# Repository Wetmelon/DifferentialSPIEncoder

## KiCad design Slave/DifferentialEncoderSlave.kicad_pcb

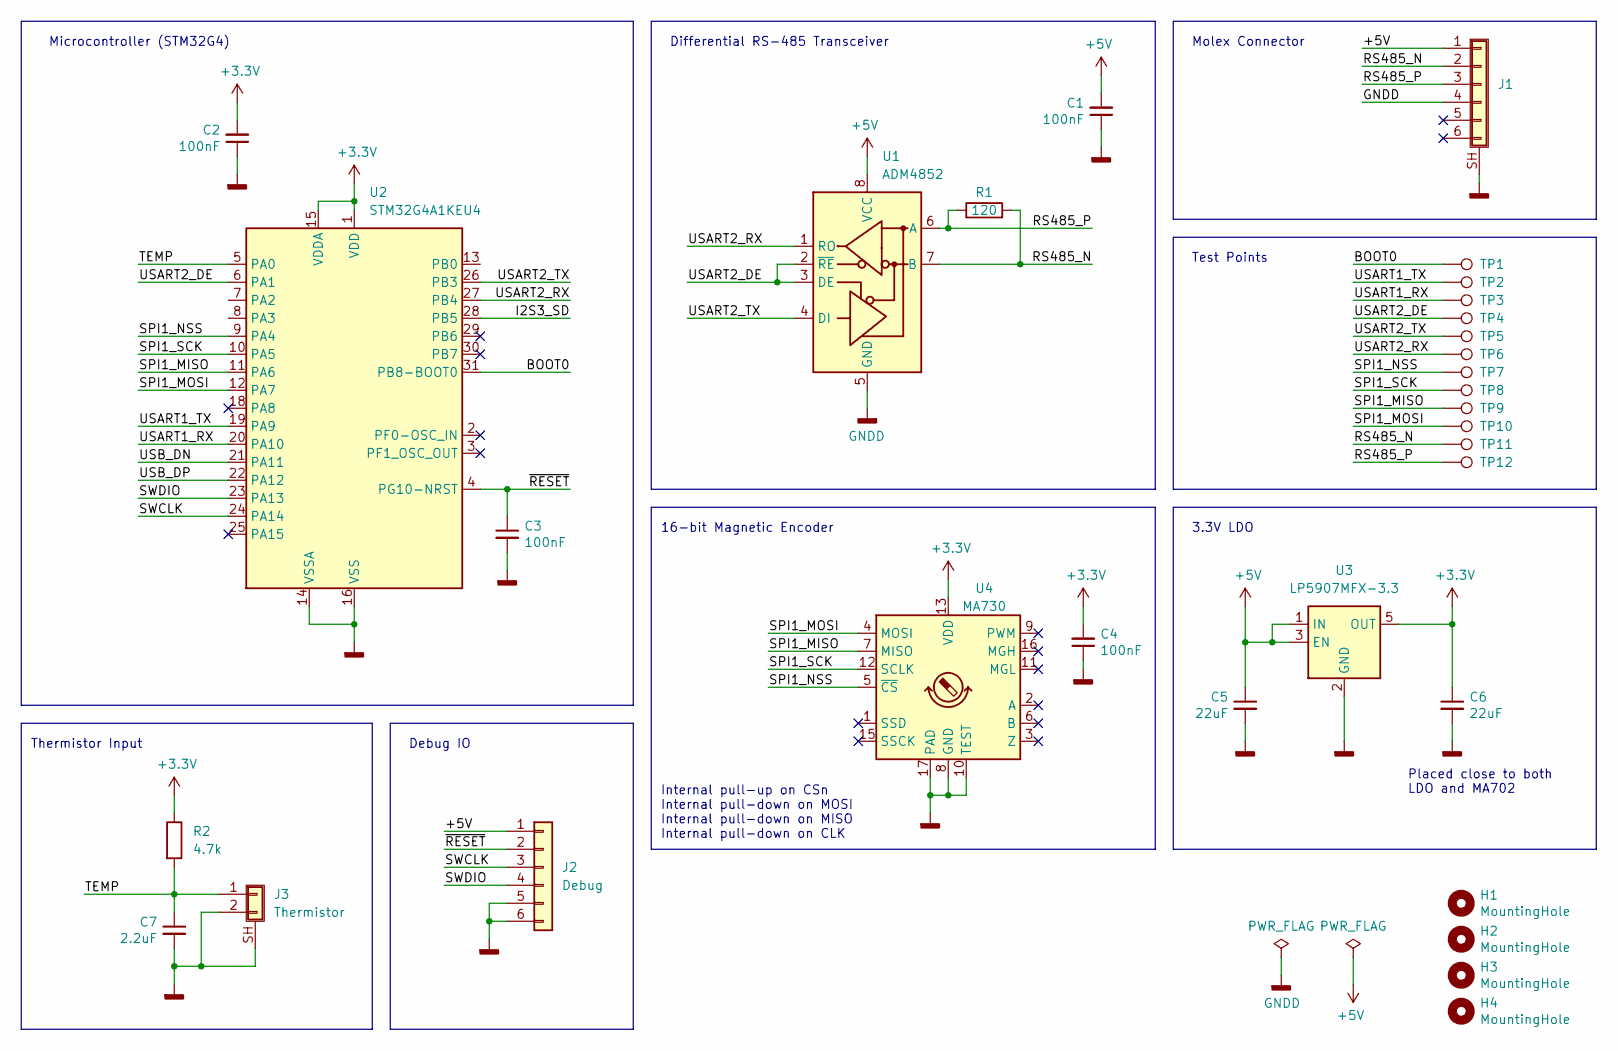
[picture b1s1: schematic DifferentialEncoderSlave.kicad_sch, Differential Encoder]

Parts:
C1, C2, C3, C4: 100nF; C_0402_1005Metric
C5, C6: 22uF; C_0805_2012Metric
C7: 2.2uF; C_0402_1005Metric
H1, H2, H3, H4: MountingHole; MountingHole_3mm
J1: (no value)
J2: Debug; Tag-Connect_TC2030-IDC-NL_2x03_P1.27mm_Vertical
J3: Thermistor; JST_GH_SM02B
R1: 120; R_0402_1005Metric
R2: 4.7k; R_0402_1005Metric
TP1, TP2, TP3, TP4, TP5, TP6, TP7, TP8, TP9, TP10, TP11, TP12: TestPoint; TestPoint_Pad_D1.0mm
U1: ADM4852; LFCSP-8-1EP_3x3mm_P0.5mm_EP1.45x1.74mm
U2: STM32G4A1KEU4; UFQFPN-32-1EP_5x5mm_P0.5mm_EP3.5x3.5mm
U3: LP5907MFX-3.3; SOT-23-5
U4: MA730; QFN-16-1EP_3x3mm_P0.5mm_EP1.7x1.7mm

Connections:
+3V3: C2.2, C4.2, C6.1, R2.1, U2.1 (VDD), U2.15 (VDDA), U2.17 (VDD), U3.5 (OUT), U4.13 (VDD)
+5V: C1.2, C5.1, J1.1, J2.1, U1.8 (VCC), U3.1 (IN), U3.3 (EN)
/BOOT0: TP1.1, U2.31 (PB8-BOOT0)
/I2S3_SD: U2.28 (PB5)
/RS485_N: J1.2, R1.2, TP11.1, U1.7 (B)
/RS485_P: J1.3, R1.1, TP12.1, U1.6 (A)
/SPI1_MISO: TP9.1, U2.11 (PA6), U4.7 (MISO)
/SPI1_MOSI: TP10.1, U2.12 (PA7), U4.4 (MOSI)
/SPI1_NSS: TP7.1, U2.9 (PA4), U4.5 (~CS)
/SPI1_SCK: TP8.1, U2.10 (PA5), U4.12 (SCLK)
/SWCLK: J2.3, U2.24 (PA14)
/SWDIO: J2.4, U2.23 (PA13)
/TEMP: C7.1, J3.1, R2.2, U2.5 (PA0)
/USART1_RX: TP3.1, U2.20 (PA10)
/USART1_TX: TP2.1, U2.19 (PA9)
/USART2_DE: TP4.1, U1.2 (~RE), U1.3 (DE), U2.6 (PA1)
/USART2_RX: TP6.1, U1.1 (RO), U2.27 (PB4)
/USART2_TX: TP5.1, U1.4 (DI), U2.26 (PB3)
/USB_DN: U2.21 (PA11)
/USB_DP: U2.22 (PA12)
/~RESET: C3.1, J2.2, U2.4 (PG10-NRST)
GNDD: C1.1, C2.1, C3.2, C4.1, C5.2, C6.2, C7.2, J1.4, J1.SH (Shield), J2.5, J2.6, J3.2, J3.SH (Shield), U1.5 (GND), U1.PAD, U2.14 (VSSA), U2.16 (VSS), U2.32 (VSS), U2.33 (PAD), U3.2 (GND), U4.8 (GND), U4.10 (TEST), U4.17 (PAD)

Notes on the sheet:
Test Points
Thermistor Input
Internal pull-up on CSn Internal pull-down on MOSI Internal pull-down on MISO Internal pull-down on CLK
16-bit Magnetic Encoder
Placed close to both LDO and MA702
3.3V LDO
Differential RS-485 Transceiver
Microcontroller (STM32G4)
Molex Connector
Debug IO

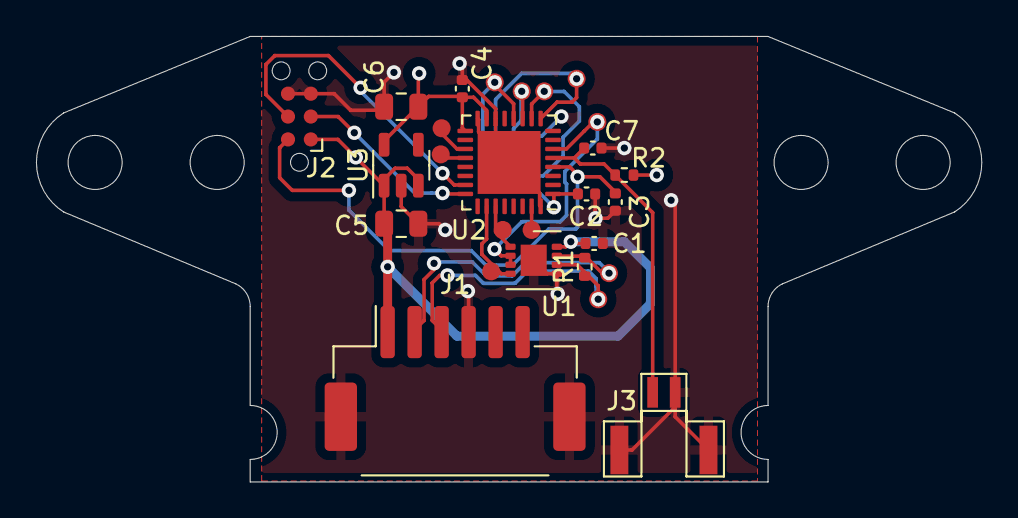
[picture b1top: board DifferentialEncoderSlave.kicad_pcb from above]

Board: 4 copper layers, 52.5 x 24.8 mm, 32 parts (1 on the bottom side), 19 nets.

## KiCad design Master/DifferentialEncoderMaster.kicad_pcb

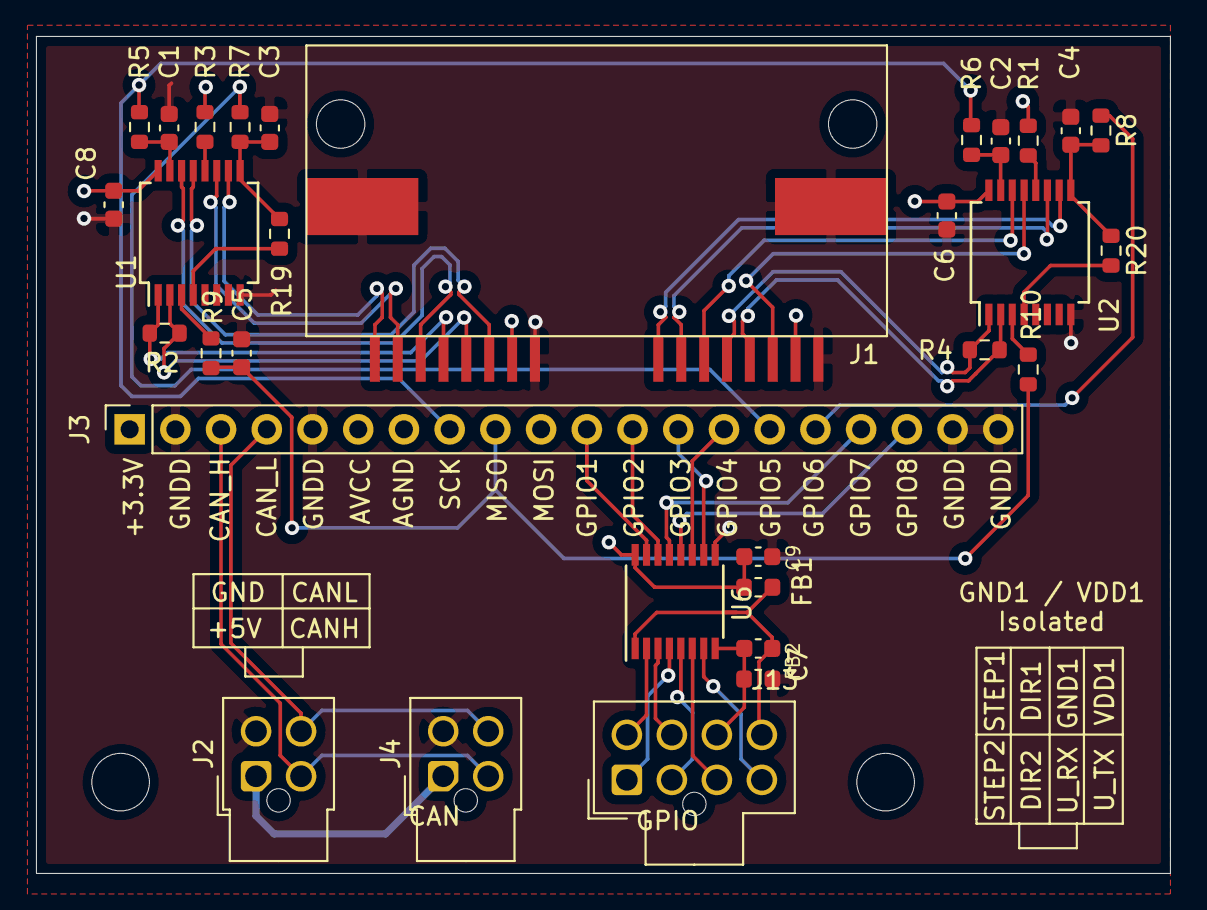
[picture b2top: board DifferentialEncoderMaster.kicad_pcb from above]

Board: 4 copper layers, 63.0 x 46.5 mm, 33 parts (0 on the bottom side), 45 nets.

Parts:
C1, C2, C3, C4, C5: 22pF; C_0603_1608Metric
C6, C7, C8, C9: 100nF; C_0603_1608Metric
FB1, FB2: 1kR; L_0603_1608Metric
H1, H2: MountingHole; MountingHole_3.2mm_M3
J1: RJ45_Shielded_x2; RJ45_RJSSE5380-02
J2, J4: CAN; Molex_Nano-Fit_105310-xx04_2x02_P2.50mm_Vertical
J3: Conn_01x20; PinSocket_1x20_P2.54mm_Vertical
J13: ISO_GPIO; Molex_Nano-Fit_105310-xx08_2x04_P2.50mm_Vertical
R1, R3: 3.3k; R_0603_1608Metric
R2, R4: 100; R_0603_1608Metric
R5, R6, R7, R8, R9, R10: 680; R_0603_1608Metric
R19, R20: 0R; R_0603_1608Metric
U1, U2: SN75C1167; SSOP-16_5.3x6.2mm_P0.65mm
U6: ISO7761DBQ; SSOP-16_3.9x4.9mm_P0.635mm

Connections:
+5V: C6.1, C8.1, C9.1, FB1.2, J1.7, J1.15, R1.1, R3.1, U1.16, U2.16, U6.16
/+12V: J2.1, J4.1
/CAN_H: J2.2, J3.3, J4.2
/CAN_L: J2.4, J3.4, J4.4
/CLK_1: C1.1, R5.2, U1.15
/CLK_1+: J1.3, U1.14
/CLK_1-: J1.6, U1.13
/CLK_2: C2.1, R6.2, U2.15
/CLK_2+: J1.11, U2.14
/CLK_2-: J1.14, U2.13
/CSn_1: C3.1, R7.2, R19.1, U1.9
/CSn_1+: J1.1, U1.10
/CSn_1-: J1.2, U1.11
/CSn_2: C4.1, R8.2, R20.1, U2.9
/CSn_2+: J1.9, U2.10
/CSn_2-: J1.10, U2.11
/GPIO1: J3.11, U6.15
/GPIO2: J3.12, U6.14
/GPIO3: J3.13, U6.10
/GPIO4: J3.14, U6.11
/GPIO5: J3.15, R7.1
/GPIO6: J3.16, R8.1
/GPIO7: J3.17, U6.13
/GPIO8: J3.18, U6.12
/ISO_DIR_1: J13.6, U6.3
/ISO_DIR_2: J13.2, U6.5
/ISO_STEP_1: J13.5, U6.2
/ISO_STEP_2: J13.1, U6.4
/ISO_UART_RX: J13.3, U6.6
/ISO_UART_TX: J13.4, U6.7
/MISO: C5.1, J3.9, R9.2, R10.2
/MISO_1: R9.1, U1.3
/MISO_1+: J1.5, R2.1, U1.2
/MISO_1-: J1.4, R2.2, U1.1
/MISO_2: R10.1, U2.3
/MISO_2+: J1.13, R4.1, U2.2
/MISO_2-: J1.12, R4.2, U2.1
/SCK: J3.8, R5.1, R6.1
GND1: C7.2, FB2.1, J13.7, U6.8
GNDD: C1.2, C2.2, C3.2, C4.2, C5.2, C6.2, C8.2, C9.2, FB2.2, J1.8, J1.16, J1.SH, J2.3, J3.2, J3.5, J3.19, J3.20, J4.3, U1.8, U2.8, U6.9
unnamed: R1.2, U2.12
unnamed: R3.2, U1.12
unnamed: R19.2, U1.4
unnamed: R20.2, U2.4
VDD1: C7.1, FB1.1, J13.8, U6.1

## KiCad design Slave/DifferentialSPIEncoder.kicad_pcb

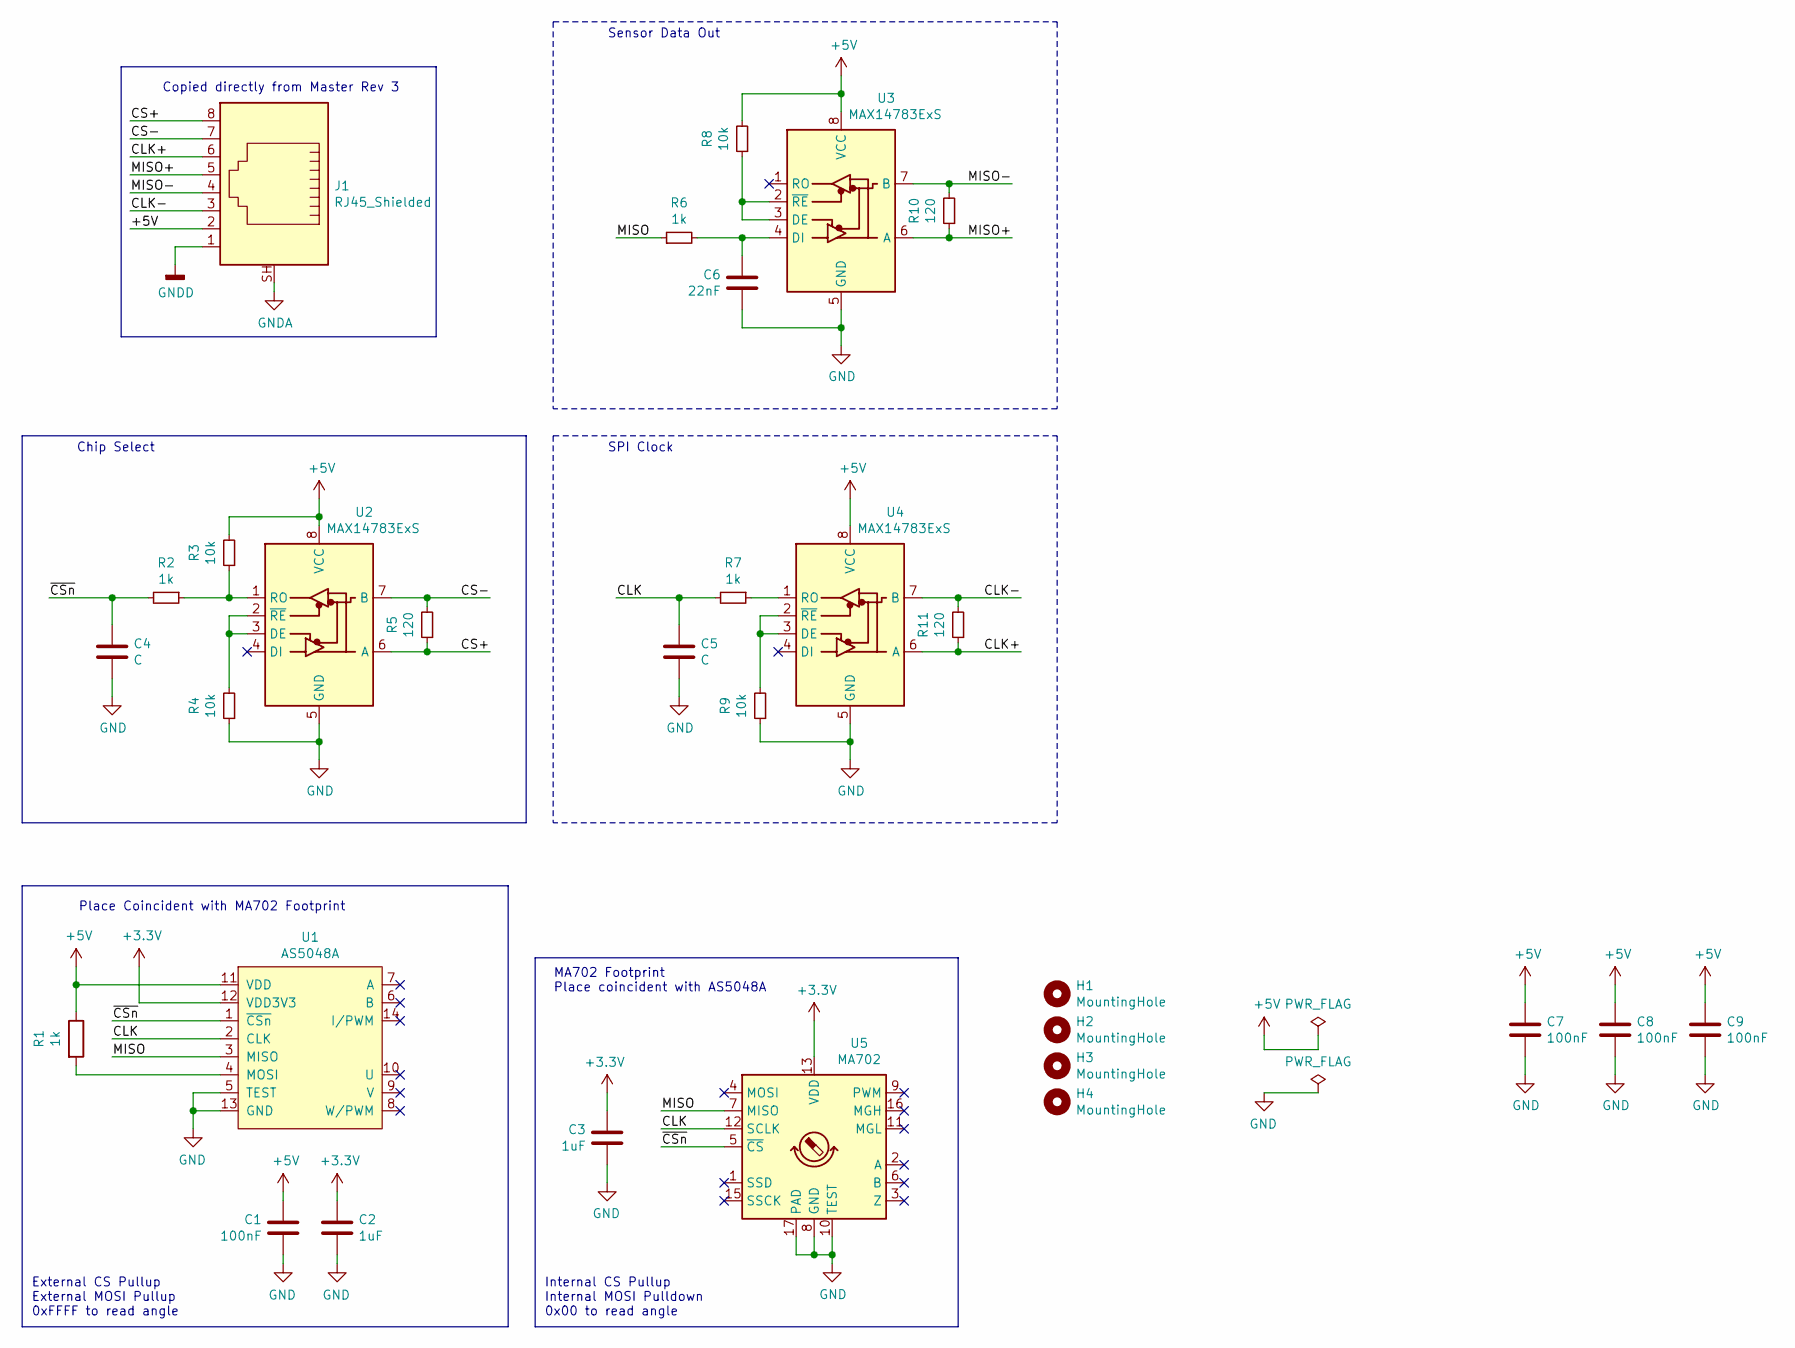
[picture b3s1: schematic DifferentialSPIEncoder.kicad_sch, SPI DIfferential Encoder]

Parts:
C1, C7, C8, C9: 100nF; C_0603_1608Metric
C2, C3: 1uF; C_0603_1608Metric
C4, C5: C; C_0603_1608Metric
C6: 22nF; C_0603_1608Metric
H1, H2: MountingHole; MountingHole_3mm
H3, H4: MountingHole; MountingHole_3.2mm_M3
J1: RJ45_Shielded; RJ45_Amphenol_RJHSE5380
R1, R2, R6, R7: 1k; R_0603_1608Metric
R3, R4, R8, R9: 10k; R_0603_1608Metric
R5, R10, R11: 120; R_0603_1608Metric
U1: AS5048A; TSSOP-14_4.4x5mm_P0.65mm
U2, U3, U4: MAX14783ExS; SOIC-8_3.9x4.9mm_P1.27mm
U5: MA702; QFN-16-1EP_3x3mm_P0.5mm_EP1.8x1.8mm

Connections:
+3V3: C2.1, C3.1, U1.12 (VDD3V3), U5.13 (VDD)
+5V: C1.1, C7.1, C8.1, C9.1, J1.2, R1.1, R3.2, R8.2, U1.11 (VDD), U2.8 (VCC), U3.8 (VCC), U4.8 (VCC)
/CLK: C5.1, R7.2, U1.2 (CLK), U5.12 (SCLK)
/CLK+: J1.6, R11.1, U4.6 (A)
/CLK-: J1.3, R11.2, U4.7 (B)
/CS+: J1.8, R5.1, U2.6 (A)
/CS-: J1.7, R5.2, U2.7 (B)
/MISO: R6.1, U1.3 (MISO), U5.7 (MISO)
/MISO+: J1.5, R10.1, U3.6 (A)
/MISO-: J1.4, R10.2, U3.7 (B)
/~CSn: C4.1, R2.2, U1.1 (~CSn), U5.5 (~CS)
GND: C1.2, C2.2, C3.2, C4.2, C5.2, C6.2, C7.2, C8.2, C9.2, R4.1, R9.1, U1.5 (TEST), U1.13 (GND), U2.5 (GND), U3.5 (GND), U4.5 (GND), U5.8 (GND), U5.10 (TEST), U5.17 (PAD)
GNDA: J1.SH
unnamed: C6.1, R6.2, U3.4 (DI)
unnamed: R1.2, U1.4 (MOSI)
unnamed: R2.1, R3.1, U2.1 (RO)
unnamed: R4.2, U2.2 (~RE), U2.3 (DE)
unnamed: R7.1, U4.1 (RO)
unnamed: R8.1, U3.2 (~RE), U3.3 (DE)
unnamed: R9.2, U4.2 (~RE), U4.3 (DE)

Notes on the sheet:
External CS Pullup External MOSI Pullup 0xFFFF to read angle
Chip Select
Place Coincident with MA702 Footprint
Copied directly from Master Rev 3
Internal CS Pullup Internal MOSI Pulldown 0x00 to read angle
MA702 Footprint Place coincident with AS5048A
Sensor Data Out
SPI Clock

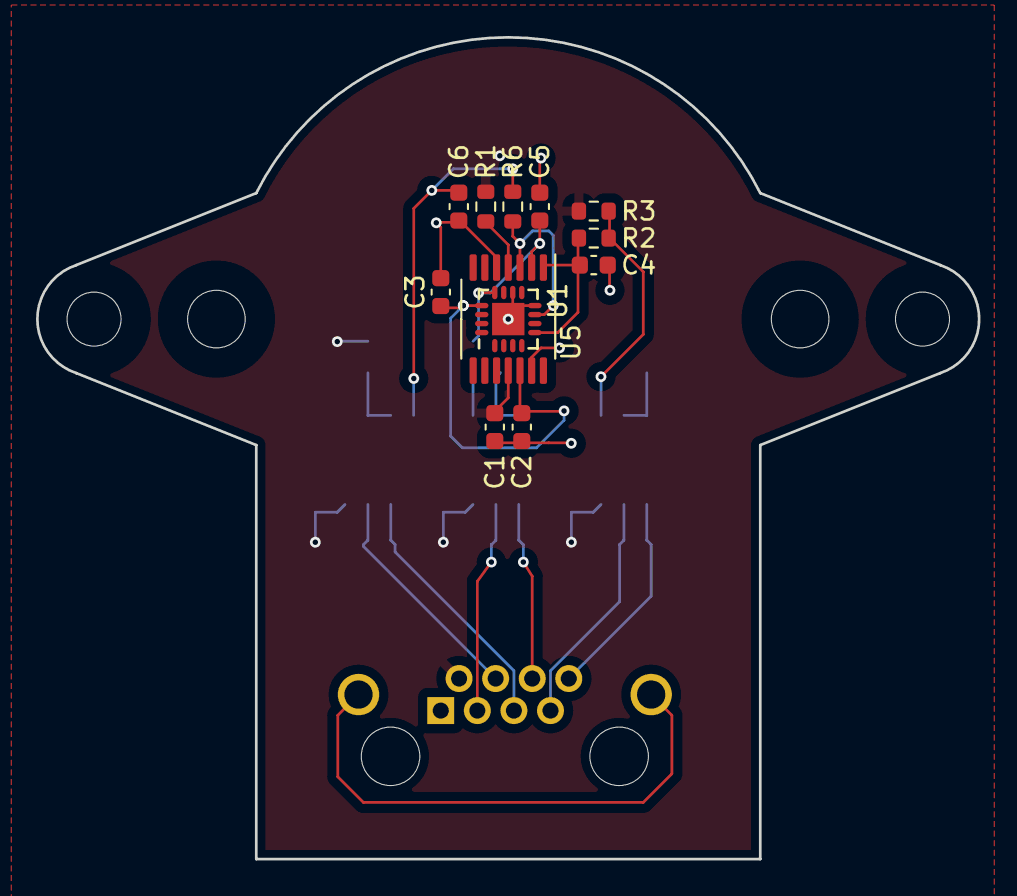
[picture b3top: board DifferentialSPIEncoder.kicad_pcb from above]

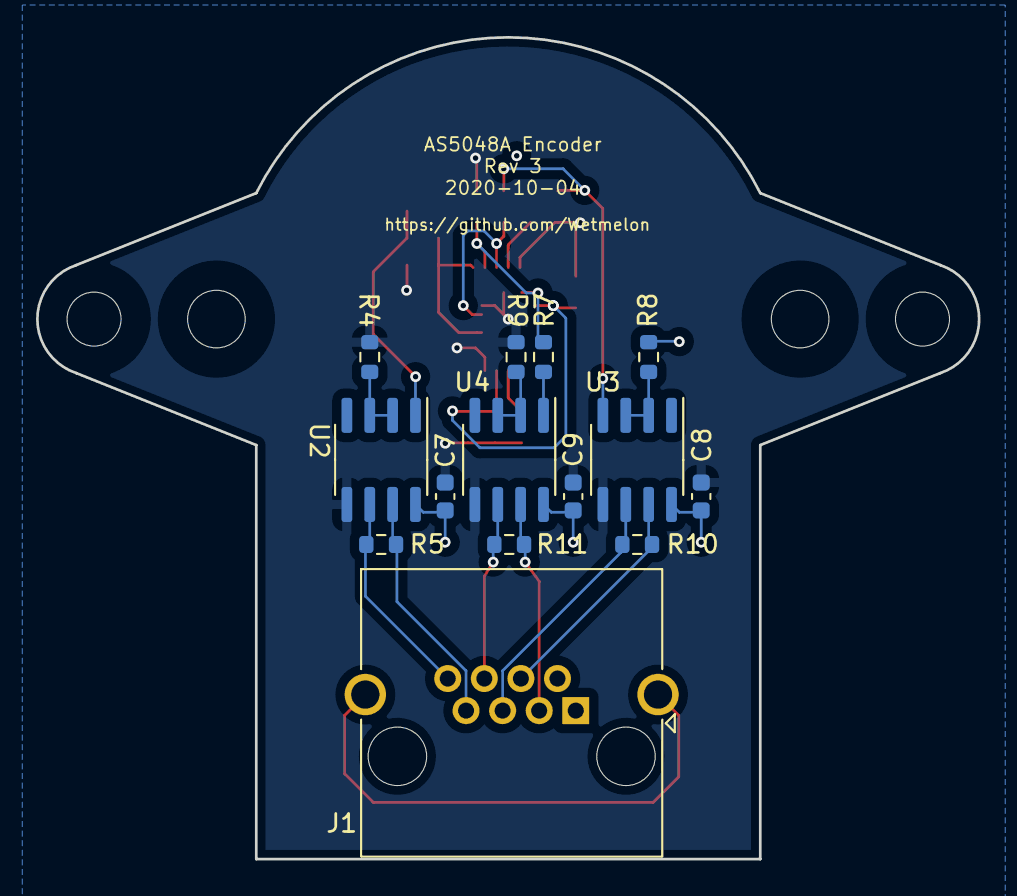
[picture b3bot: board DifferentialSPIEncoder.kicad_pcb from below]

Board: 2 copper layers, 52.3 x 45.7 mm, 30 parts (14 on the bottom side), 19 nets.

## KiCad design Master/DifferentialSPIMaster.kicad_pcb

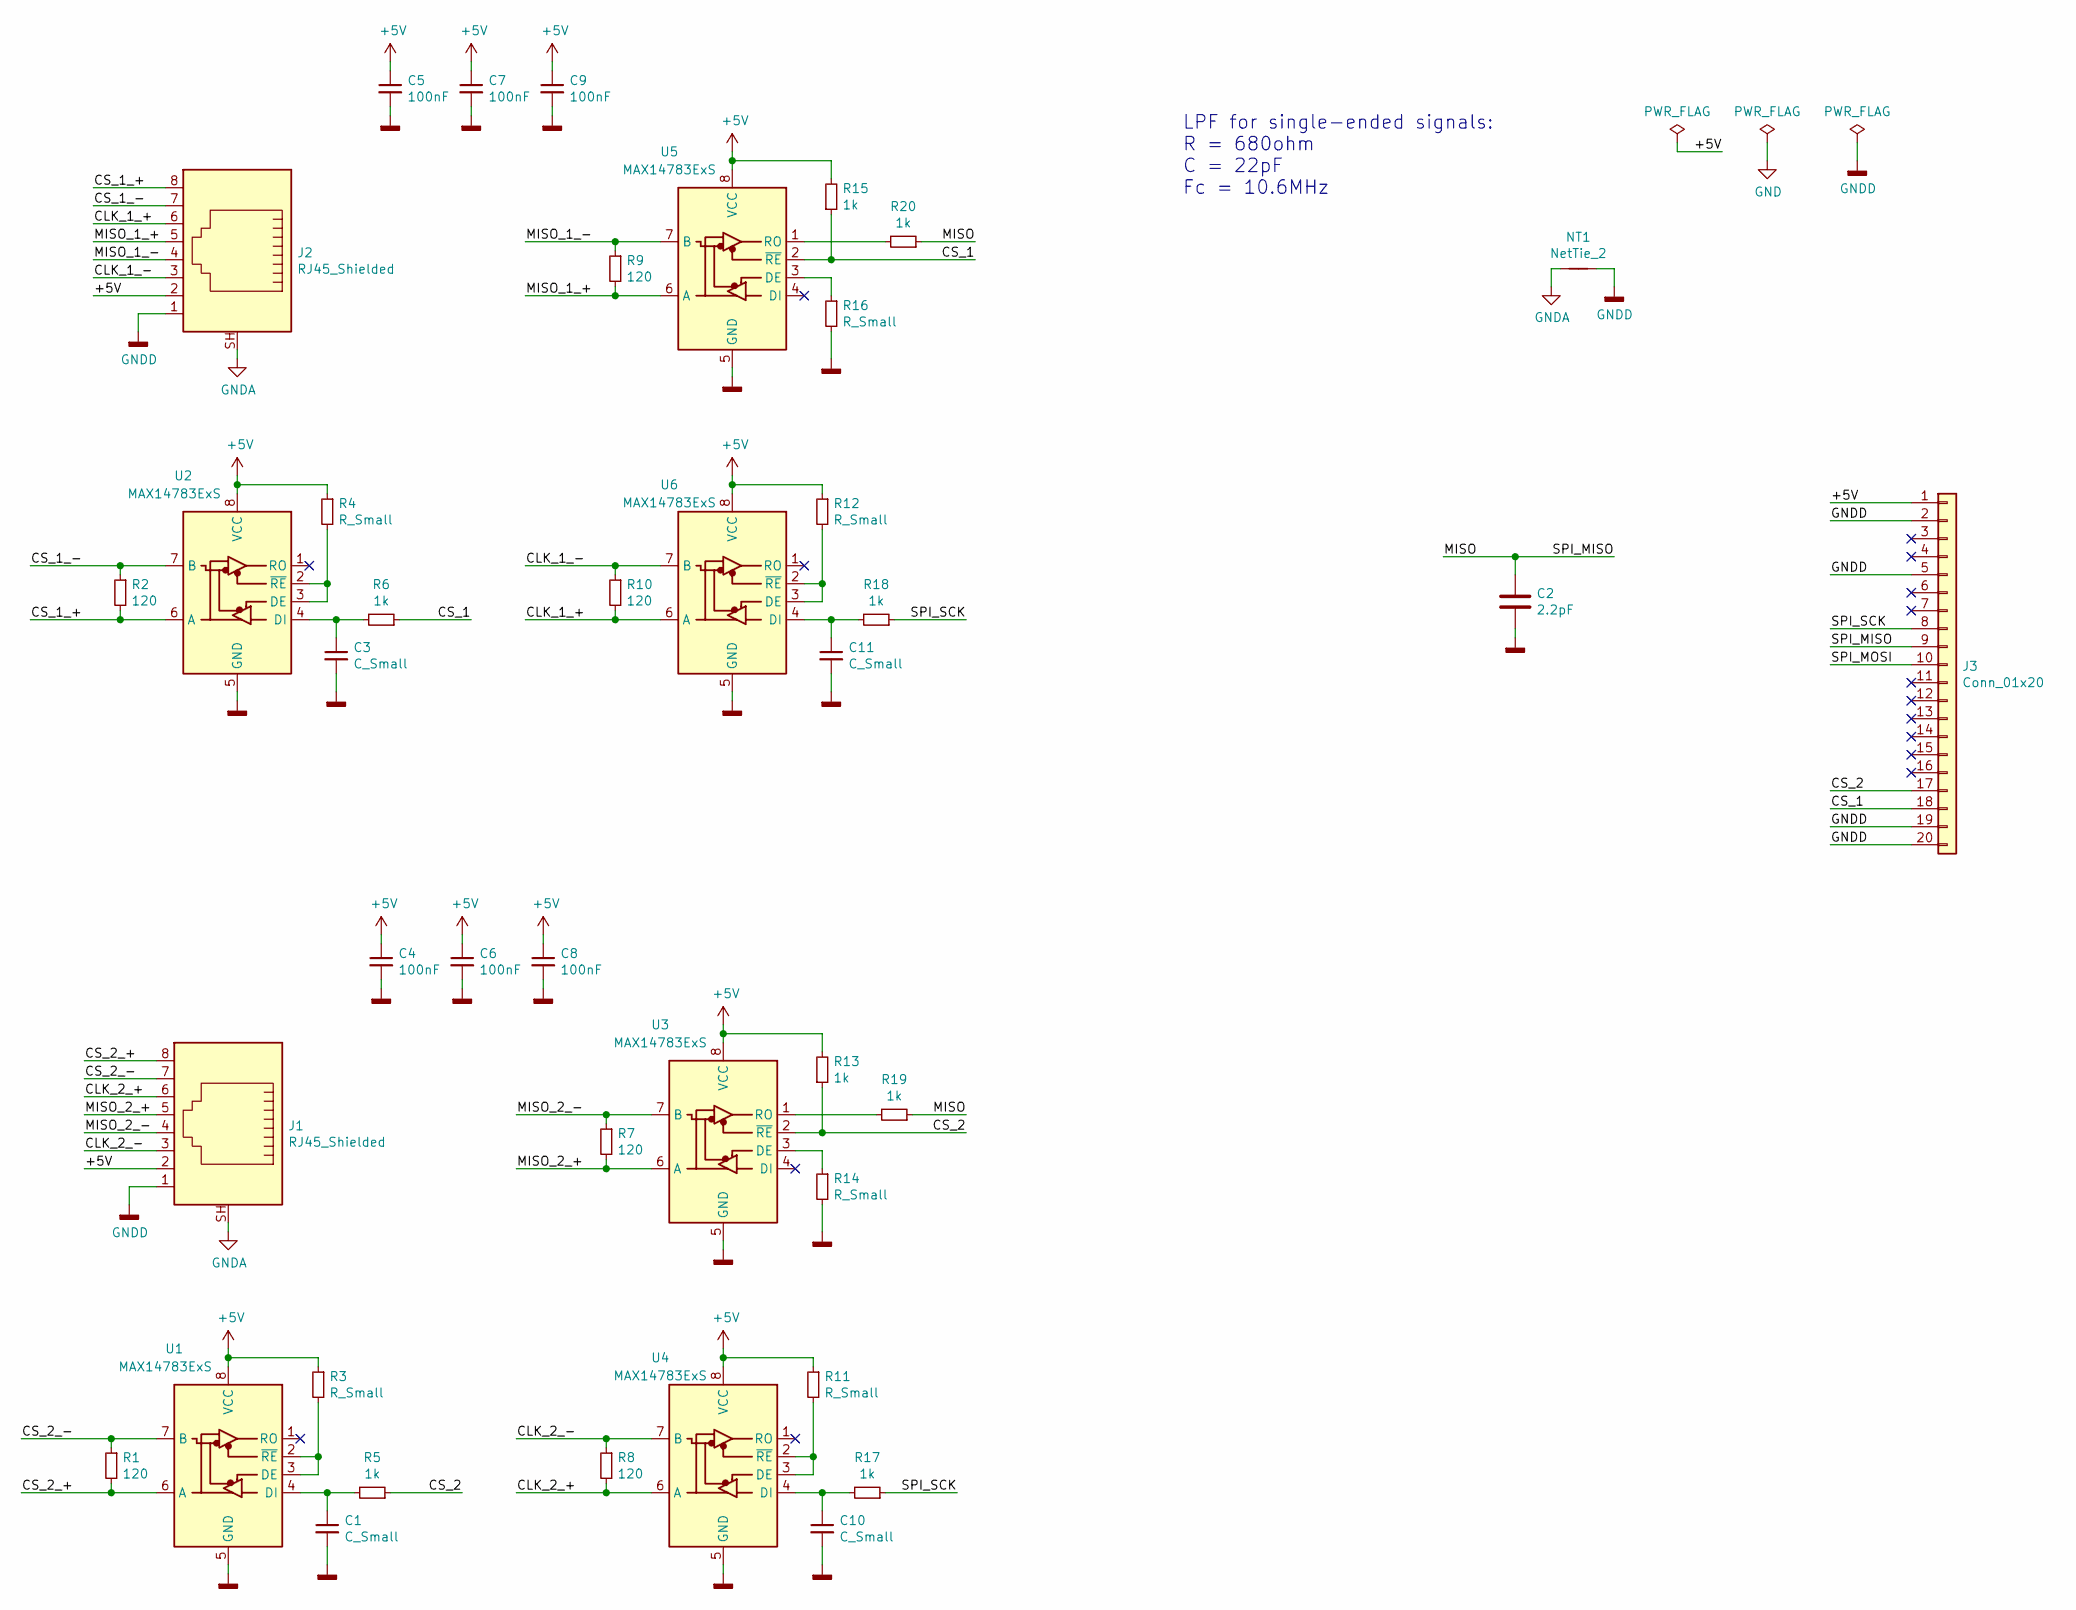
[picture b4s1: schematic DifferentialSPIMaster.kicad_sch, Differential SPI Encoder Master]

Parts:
C1, C3, C10, C11: C_Small; C_0805_2012Metric_Pad1.15x1.40mm_HandSolder
C2: 2.2pF; C_0805_2012Metric_Pad1.15x1.40mm_HandSolder
C4, C5, C6, C7, C8, C9: 100nF; C_0805_2012Metric_Pad1.15x1.40mm_HandSolder
J1, J2: RJ45_Shielded; RJ45_Amphenol_RJHSE5380
J3: Conn_01x20; PinSocket_1x20_P2.54mm_Vertical
NT1: NetTie_2; NetTie-2_SMD_Pad0.5mm
R1, R2, R7, R8, R9, R10: 120; R_0805_2012Metric_Pad1.15x1.40mm_HandSolder
R3, R4, R11, R12, R14, R16: R_Small; R_0805_2012Metric_Pad1.15x1.40mm_HandSolder
R5, R6, R13, R15, R17, R18, R19, R20: 1k; R_0805_2012Metric_Pad1.15x1.40mm_HandSolder
U1, U2, U3, U4, U5, U6: MAX14783ExS; SOIC-8_3.9x4.9mm_P1.27mm

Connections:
+5V: C4.1, C5.1, C6.1, C7.1, C8.1, C9.1, J1.2, J2.2, J3.1, R3.1, R4.1, R11.1, R12.1, R13.2, R15.2, U1.8 (VCC), U2.8 (VCC), U3.8 (VCC), U4.8 (VCC), U5.8 (VCC), U6.8 (VCC)
/CLK_1_+: J2.6, R10.2, U6.6 (A)
/CLK_1_-: J2.3, R10.1, U6.7 (B)
/CLK_2_+: J1.6, R8.2, U4.6 (A)
/CLK_2_-: J1.3, R8.1, U4.7 (B)
/CS_1: J3.18, R6.1, R15.1, U5.2 (~RE)
/CS_1_+: J2.8, R2.2, U2.6 (A)
/CS_1_-: J2.7, R2.1, U2.7 (B)
/CS_2: J3.17, R5.1, R13.1, U3.2 (~RE)
/CS_2_+: J1.8, R1.2, U1.6 (A)
/CS_2_-: J1.7, R1.1, U1.7 (B)
/MISO: C2.1, J3.9, R19.1, R20.1
/MISO_1_+: J2.5, R9.2, U5.6 (A)
/MISO_1_-: J2.4, R9.1, U5.7 (B)
/MISO_2_+: J1.5, R7.2, U3.6 (A)
/MISO_2_-: J1.4, R7.1, U3.7 (B)
/SPI_SCK: J3.8, R17.1, R18.1
GNDA: J1.SH, J2.SH, NT1.1
GNDD: C1.2, C2.2, C3.2, C4.2, C5.2, C6.2, C7.2, C8.2, C9.2, C10.2, C11.2, J1.1, J2.1, J3.2, J3.5, J3.19, J3.20, NT1.2, R14.2, R16.2, U1.5 (GND), U2.5 (GND), U3.5 (GND), U4.5 (GND), U5.5 (GND), U6.5 (GND)
unnamed: C1.1, R5.2, U1.4 (DI)
unnamed: C3.1, R6.2, U2.4 (DI)
unnamed: C10.1, R17.2, U4.4 (DI)
unnamed: C11.1, R18.2, U6.4 (DI)
unnamed: R3.2, U1.2 (~RE), U1.3 (DE)
unnamed: R4.2, U2.2 (~RE), U2.3 (DE)
unnamed: R11.2, U4.2 (~RE), U4.3 (DE)
unnamed: R12.2, U6.2 (~RE), U6.3 (DE)
unnamed: R14.1, U3.3 (DE)
unnamed: R16.1, U5.3 (DE)
unnamed: R19.2, U3.1 (RO)
unnamed: R20.2, U5.1 (RO)

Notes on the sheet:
LPF for single-ended signals: R = 680ohm C = 22pF Fc = 10.6MHz

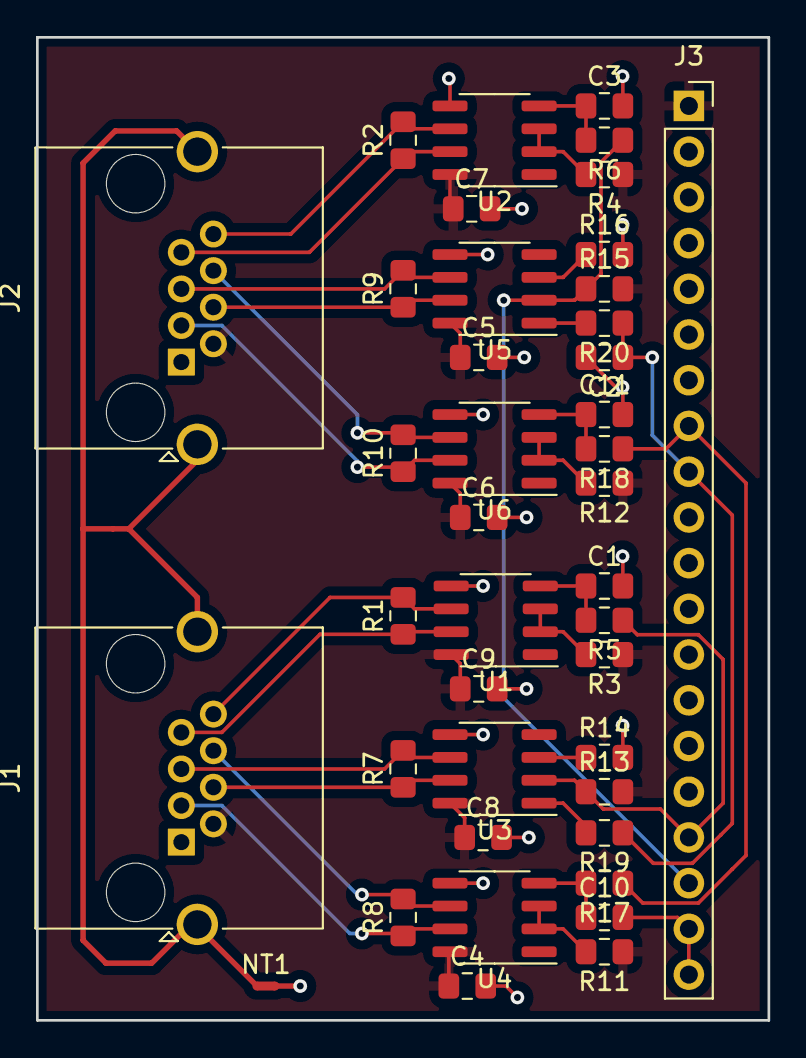
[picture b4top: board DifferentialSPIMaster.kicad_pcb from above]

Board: 2 copper layers, 40.6 x 54.6 mm, 41 parts (0 on the bottom side), 31 nets.

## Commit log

2019-06-01 Create LICENSE
2019-06-01 Fix voltage pins on Master
2019-06-04 Add / update PDFs
2019-06-06 Add LPFs to single-ended signals
2019-06-06 Update PDF for slave
2019-06-09 Start laying out Master
2019-10-13 CS transceivers now correctly setup to transmit, not receive
2019-10-14 new stuff
2019-10-14 nother commit
2019-10-14 next version
2019-10-15 fixed mounting holes
2019-10-18 converted to +5v only
2019-10-20 Shame. Shame. Shame.
2019-10-21 CLK is an output, not an input on master, also add edge cuts layer
2019-10-21 Fix silkscreen
2019-10-21 Move board edge closer to RJ45s
2019-10-26 Add top/bottom fills, make board 2 layer
2019-11-02 adding stub
    .
2019-11-02 Create tmp
    .
2019-11-02 added gerbers
2019-11-02 removing stub
    .
2019-11-02 remove stub
    .
2019-11-07 Added values for LPFs
2019-11-07 add BOM for parts
2019-12-02 Update master schematic with changes from #2
2019-12-02 Update slave schematic with changes from #2
2019-12-02 Replace MAX485E with SN65HVD06D for 10mbps signaling
2019-12-02 Fit slave to AMT102 footprint
2019-12-02 Finish slave layout
2019-12-02 Tweaks to layout to better fit AMT footprint
2019-12-02 Add silkscreen with info
2019-12-03 Move copper pours inboard to avoid screw heads
2019-12-03 Swap AS5048A with AS5047U
2019-12-03 Some tweaks
2019-12-05 Add pullups for CS lines and remove extra material from master
2019-12-05 differential tuning on master
2020-07-22 Swap to MAX14783E
2020-07-22 Update PCB
2020-07-22 Swap to MAX14783 on Master
2020-07-22 Ignore .sch-bak files
2020-10-04 Update master
2020-10-04 re-save under nightly
2020-10-04 remove .dxfs
2020-10-04 Remove gerbers
2020-10-04 Fix Slave
2020-10-04 Ignore backups
2020-10-04 Revert to older build of Kicad
2020-10-04 Revert slave pcb to older build of Kicad
2020-10-04 Finish encoder side layout
2020-10-23 restart Master side layout in older kicad version
2020-10-27 Make ODrive side full board length, add diff. incremental
2020-10-27 Minor change to encoder transceiver
2020-10-28 Add digital isolators
2020-11-09 Big updates to master
2020-11-09 Finish rev 1 layout
2020-11-09 Rotate board and recreate planes
2020-11-09 Minor changes to silkscreen etc
2020-12-05 Update Slave
2020-12-05 Minor chagnes
2020-12-06 Update board outline
2020-12-06 Use 3mm holes
2020-12-06 Update Slave with circular keepout, SMD RJ 45
2020-12-06 Make the body narrower
2020-12-17 Export master BOM
2020-12-17 Make the encoder 1.3mm shorter to make it flush with the case
2021-04-08 Encoder side TSSOP -> SOP 5.3x6.2
2021-04-08 Odrive side TSSOP->SSOP
2021-04-08 Remove differential encoder half
2021-04-08 Optimize layout - remove ~ 15% of vias
2021-04-08 Further layout optimization
2021-04-08 Prettify CAN wires
2021-05-22 Create AEAT-9922 encoder variant
2022-04-17 Start RS485 revision
2022-04-18 Finish laying out encoder board
2022-04-24 Change pinout on STM32G4, add thermistor header, add test points
2022-04-24 Add narrow mounting holes
2022-04-24 Add RS485 termination resistor
2022-04-24 Ground CLIK-Mate shield pins
2022-04-25 Silkscreen fixes
